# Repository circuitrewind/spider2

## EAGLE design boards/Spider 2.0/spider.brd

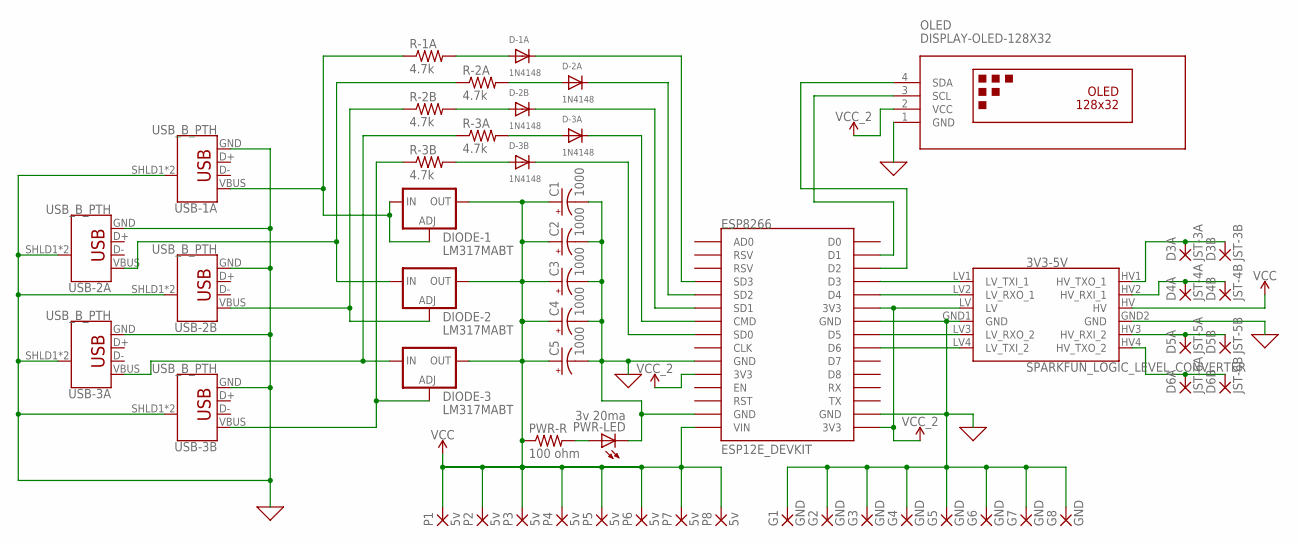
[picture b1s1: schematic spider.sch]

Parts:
3V3-5V: SPARKFUN_LOGIC_LEVEL_CONVERTER
C1, C2, C3, C4, C5: 1000; E3,5-8
D3A: JST-3A; 2,54/1,1
D3B: JST-3B; 2,54/1,1
D4A: JST-4A; 2,54/1,1
D4B: JST-4B; 2,54/1,1
D5A: JST-5A; 2,54/1,1
D5B: JST-5B; 2,54/1,1
D6A: JST-6A; 2,54/1,1
D6B: JST-6B; 2,54/1,1
D-1A, D-2A, D-2B, D-3A, D-3B: 1N4148; DO-1N4148
DIODE-1, DIODE-2, DIODE-3: LM317MABT; TO220L1
ESP8266: ESP12E_DEVKIT
G1, G2, G3, G4, G5, G6, G7, G8: GND; 2,54/1,1
OLED: DISPLAY-OLED-128X32
P1, P2, P3, P4, P5, P6, P7, P8: 5v; 2,54/1,1
PWR-LED: 3v 20ma; LED3MM
PWR-R: 100 ohm; 0204/7
R-1A, R-2A, R-2B, R-3A, R-3B: 4.7k; 0207/7
USB-1A, USB-2A, USB-2B, USB-3A, USB-3B: USB_B_PTH; USB-B-PTH

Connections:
3V3: 3V3-5V.LV, ESP8266.3V3@0 (3V3), ESP8266.3V3@1 (3V3), ESP8266.3V3@2 (3V3), OLED.2 (VCC)
D3-3V: 3V3-5V.LV1 (LV_TXI_1), ESP8266.D3
D3-5V: 3V3-5V.HV1 (HV_TXO_1), D3A.1, D3B.1
D4-3V: 3V3-5V.LV2 (LV_RXO_1), ESP8266.D4
D4-5V: 3V3-5V.HV2 (HV_RXI_1), D4A.1, D4B.1
D5-3V: 3V3-5V.LV3 (LV_RXO_2), ESP8266.D5
D5-5V: 3V3-5V.HV3 (HV_RXI_2), D5A.1, D5B.1
D6-3V: 3V3-5V.LV4 (LV_TXI_2), ESP8266.D6
D6-5V: 3V3-5V.HV4 (HV_TXO_2), D6A.1, D6B.1
GND: 3V3-5V.GND1 (GND), 3V3-5V.GND2 (GND), C1.-, C2.-, C3.-, C4.-, C5.-, ESP8266.GND@0 (GND), ESP8266.GND@1 (GND), ESP8266.GND@2 (GND), ESP8266.GND@3 (GND), G1.1, G2.1, G3.1, G4.1, G5.1, G6.1, G7.1, G8.1, OLED.1 (GND), PWR-LED.K (C), USB-1A.GND, USB-1A.SHLD1 (SHIELD), USB-1A.SHLD2 (SHIELD), USB-2A.GND, USB-2A.SHLD1 (SHIELD), USB-2A.SHLD2 (SHIELD), USB-2B.GND, USB-2B.SHLD1 (SHIELD), USB-2B.SHLD2 (SHIELD), USB-3A.GND, USB-3A.SHLD1 (SHIELD), USB-3A.SHLD2 (SHIELD), USB-3B.GND, USB-3B.SHLD1 (SHIELD), USB-3B.SHLD2 (SHIELD)
NET-1A: D-1A.A, R-1A.2
NET-2A: D-2A.A, R-2A.2
NET-2B: D-2B.A, R-2B.2
NET-3A: D-3A.A, R-3A.2
NET-3B: D-3B.A, R-3B.2
OLED-SCL: ESP8266.D1, OLED.3 (SCL)
OLED-SDA: ESP8266.D2, OLED.4 (SDA)
PWR-LED: PWR-LED.A, PWR-R.2
VBUS-1A: DIODE-1.1 (ADJ), DIODE-1.3 (IN), R-1A.1, USB-1A.VBUS
VBUS-2A: DIODE-2.3 (IN), R-2A.1, USB-2A.VBUS
VBUS-2B: DIODE-2.1 (ADJ), R-2B.1, USB-2B.VBUS
VBUS-3A: DIODE-3.3 (IN), R-3A.1, USB-3A.VBUS
VBUS-3B: DIODE-3.1 (ADJ), R-3B.1, USB-3B.VBUS
VCC: 3V3-5V.HV, C1.+, C2.+, C3.+, C4.+, C5.+, DIODE-1.2 (OUT), DIODE-2.2 (OUT), DIODE-3.2 (OUT), ESP8266.VIN, P1.1, P2.1, P3.1, P4.1, P5.1, P6.1, P7.1, P8.1, PWR-R.1
VIN-1A: D-1A.C, ESP8266.SD3
VIN-2A: D-2A.C, ESP8266.SD2
VIN-2B: D-2B.C, ESP8266.SD1
VIN-3A: D-3A.C, ESP8266.CMD
VIN-3B: D-3B.C, ESP8266.SD0

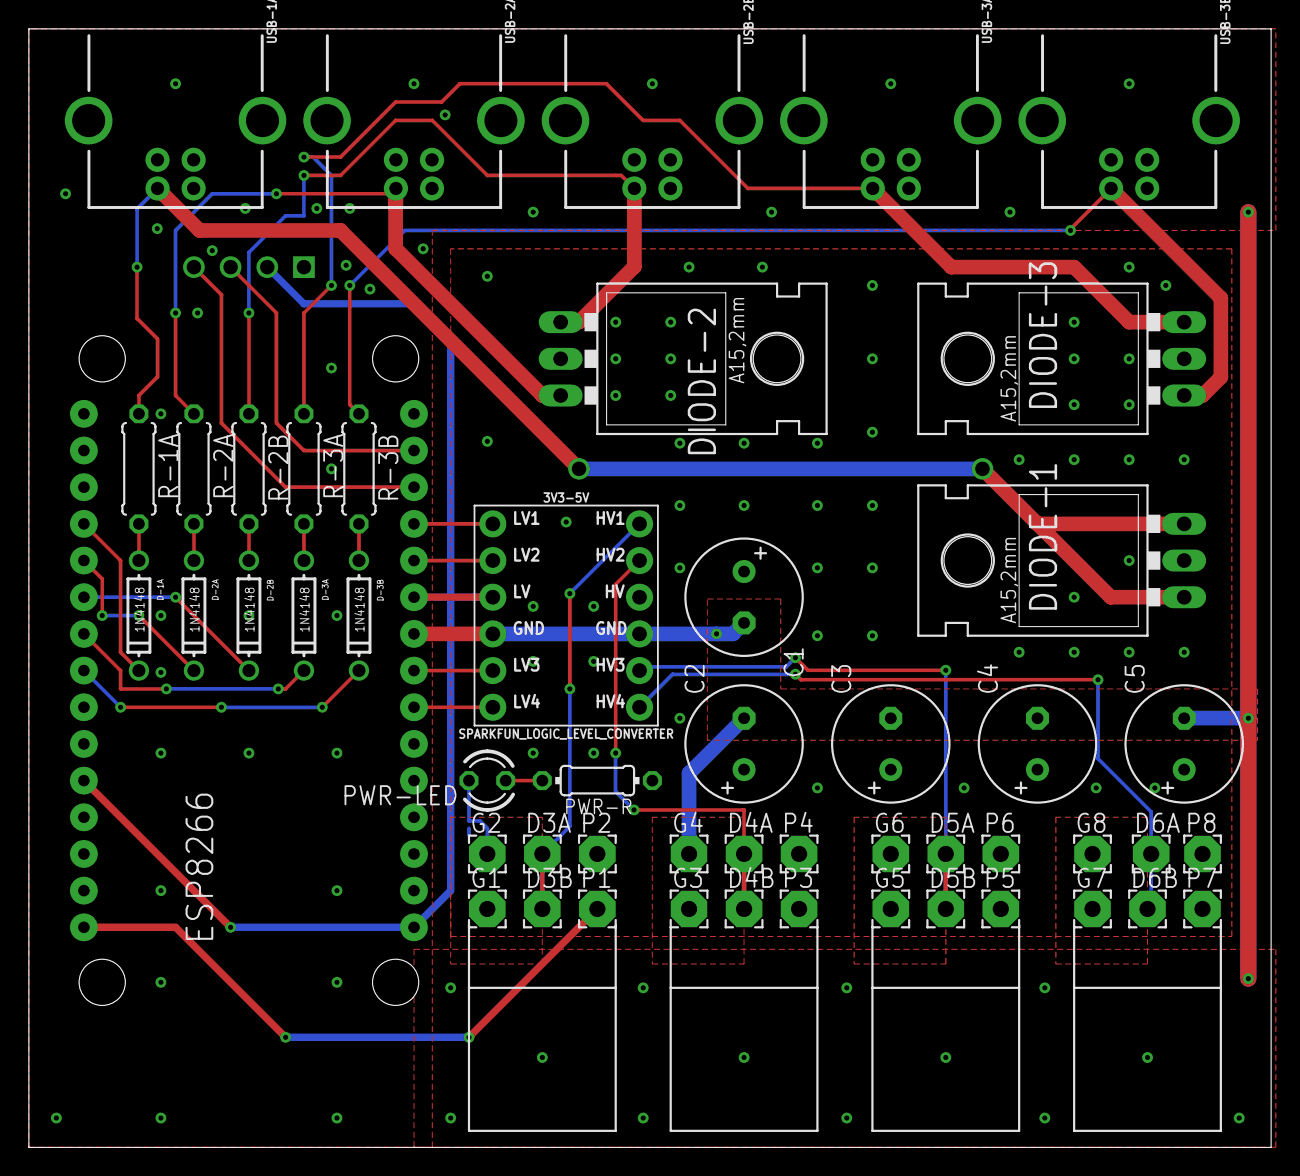
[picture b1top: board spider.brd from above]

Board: 2 copper layers, 86.0 x 77.5 mm, 52 parts (1 on the bottom side), 29 nets.

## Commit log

2019-03-19 new root commit
2019-03-19 Updating config.json
2019-03-19 Remove HTTP_POST from web server
2019-03-19 Server code updating for changes in ESP8266WebServer Relies more upon (char*) instead of (String)
2019-03-19 Updating Lua to be able to be reinitialized
2019-03-19 Check for nullptr pointers and null values
2019-03-19 No more F() support for has Args (temporary)
2019-03-19 Added paths for ESP 8266 module
2019-03-19 Disabled default route
2019-03-19 Updating submodules
2019-03-19 Disable auto correction on script editor
2019-03-19 Updating scripts
2019-03-19 Removing old wifi pinging code
2019-03-19 Adding example config for grid layout
2019-03-19 Updating for latest ESP8266WebServer
2019-03-19 Initial support for new config options
2019-03-19 Updating HTTP API
2019-03-19 Updating to latest LUA library This fixes the corrupt string issue
2019-03-19 Little bits of cleanup and removing debug code
2019-03-19 Updating Lua
2019-03-19 Adding todo notes
2019-03-19 Adding web server to project editor. This allows me to more easily re-write the ESP8266WebServer
2019-03-19 Adding pingalive submodule This helps keep wifi stable
2019-04-04 Updating for ArduinoJson v6
2019-04-09 Adding Autodesk Eagle files for the Spider Board 2.0
2019-04-10 Switching from generic text area over to Ace editor
    Source:
    https://ace.c9.io

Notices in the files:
boards/Spider 2.0/spider.brd:
© 2017 Darkain Multimedia
parts and their libraries:
SparkFun-Boards: Licensing: Creative Commons ShareAlike 4.0 International - https://creativecommons.org/licenses/by-sa/4.0
diy-modules: Released under the Creative Commons Attribution 4.0 International License: http://creativecommons.org/licenses/by/4.0
